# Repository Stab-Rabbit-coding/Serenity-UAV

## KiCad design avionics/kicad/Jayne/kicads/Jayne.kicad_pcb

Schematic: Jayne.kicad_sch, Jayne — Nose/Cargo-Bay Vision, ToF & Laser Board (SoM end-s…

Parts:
CMC5: SRF2012-100Y (CAN); L_CommonModeChoke_Coilcraft_0805USB
C_2V5I, C_2V5O: 1uF; C_0402_1005Metric
C_ISO: 100nF/500V; C_0402_1005Metric
C_VCORE: 1uF; C_0402_1005Metric
C_VISO: 1uF; C_0402_1005Metric
D5: PRTR5V0U2X (CAN); SOT-363_SC-70-6
J_CAM1: CSI CLK/D0; JST_GH_BM04B-GHS-TBT_1x04-1MP_P1.25mm_Vertical
J_CAM2: CAM SDA/SCL/RST/3V3; JST_GH_BM04B-GHS-TBT_1x04-1MP_P1.25mm_Vertical
J_CAM_DS: Direct-solder camera land (nose; DNP if J_CAM* us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; DS_Camera_9P
J_CANFD: 5V/CANH/CANL/GND; JST_GH_BM04B-GHS-TBT_1x04-1MP_P1.25mm_Vertical
J_CHASSIS_R: 0R; R_0402_1005Metric
J_ETH_IN: JST-GH 5P shielded Eth ring; JST_GH_SM05B-GHS-TB_1x05-1MP_P1.25mm_Horizontal
J_ETH_OUT: JST-GH 5P shielded Eth ring; JST_GH_SM05B-GHS-TB_1x05-1MP_P1.25mm_Horizontal
J_LASER: laser +5V/cathode; JST_SH_BM02B-SRSS-TB_1x02-1MP_P1.00mm_Vertical
J_LASER_DS: Direct-solder laser land (nose; DNP if J_LASER us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; DS_Laser_2P
J_PWR: JST-GH 2P +5V/GND; JST_GH_BM02B-GHS-TBT_1x02-1MP_P1.25mm_Vertical
J_SWD: SWD: DIO/CLK/NRST/GND; JST_GH_BM04B-GHS-TBT_1x04-1MP_P1.25mm_Vertical
J_TOF: TFmini-S 5V/GND/TX/RX; JST_GH_BM04B-GHS-TBT_1x04-1MP_P1.25mm_Vertical
J_TOF_DS: Direct-solder ToF land (nose; DNP if J_TOF used); DS_ToF_4P
Q1: AO3400 logic-level N-MOSFET; SOT-23
R1: 100R gate; R_0402_1005Metric
R2: 10k pulldown; R_0402_1005Metric
R_FB1B, R_FB3B: R_fbbot; R_0402_1005Metric
R_FB1T, R_FB3T: R_fbtop; R_0402_1005Metric
R_ISET: 6.04k; R_0402_1005Metric
R_NRST: 10k; R_0402_1005Metric
R_PG1, R_PG3: 100k; R_0402_1005Metric
R_PORZ: 10k; R_0402_1005Metric
R_REXT: 191R; R_0402_1005Metric
R_SHIELD: 0R; R_0402_1005Metric
T1, T2: Wurth 749010012A; Wurth_749010012A_10-100BASE-TX
T1_CMC1, T1_CMC2, T2_CMC1, T2_CMC2: SRF2012-100Y; L_CommonModeChoke_Coilcraft_0805USB
T1_D1, T1_D2, T2_D1, T2_D2: PRTR5V0U2X; SOT-363_SC-70-6
U2: Microchip KSZ9477; TQFP-128-1EP_KSZ9477_14x14mm_P0.4mm_EP10x10
U3: TI MSPM0G3507; QFN-48-1EP_7x7mm_P0.5mm_EP5.15x5.15mm
U4: TI ISOW1044BDFMR; SOIC-20W_7.5x12.8mm_P1.27mm
U5: Infineon SLB9670; QFN-32-1EP_5x5mm_P0.5mm_EP3.45x3.45mm
U_REG_1V2: TLV62569 -> +1V2; SOT-23-6
U_REG_1V2_CI, U_REG_3V3_CI: 10uF; C_0402_1005Metric
U_REG_1V2_CO, U_REG_3V3_CO: 22uF; C_0402_1005Metric
U_REG_1V2_L, U_REG_3V3_L: 2.2uH; L_Taiyo-Yuden_NR-20xx
U_REG_2V5: TLV75725 -> +2V5; SOT-23-5
U_REG_3V3: TLV62569 -> +3V3; SOT-23-6
U_SOM: phyCORE-AM62x PCM-071; phyCORE-AM62x_PCM071_2xBTH-060
Y1: 25MHz; Crystal_SMD_2012-2Pin_2.0x1.2mm

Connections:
+1V2: R_FB1T.1, R_PG1.1, U2.3 (AVDDL), U2.11 (DVDDL), U2.14 (AVDDL), U2.19 (AVDDL), U2.23 (DVDDL), U2.30 (AVDDL), U2.36 (AVDDL), U2.41 (AVDDL), U2.45 (DVDDL), U2.56 (DVDDL), U2.66 (DVDDL), U2.70 (DVDDL), U2.71 (VDDLS), U2.84 (VDDLS), U2.87 (DVDDL), U2.104 (DVDDL), U2.110 (DVDDL), U2.114 (AVDDL), U2.119 (AVDDL), U2.124 (AVDDL), U_REG_1V2_CO.1, U_REG_1V2_L.2
+1V2_PG: R_PG1.2, U_REG_1V2.6 (PG)
+2V5: C_2V5O.1, U2.10 (AVDDH), U2.22 (AVDDH), U2.33 (AVDDH), U2.44 (AVDDH), U2.72 (VDDHS), U2.83 (VDDHS), U2.111 (AVDDH), U2.122 (AVDDH), U2.128 (AVDDH), U_REG_2V5.5 (OUT)
+3V3: C_2V5I.1, J_CAM2.4, J_CAM_DS.8, R_FB3T.1, R_NRST.1, R_PG3.1, R_PORZ.1, U2.61 (VDDIO), U2.68 (VDDIO), U2.99 (VDDIO), U3.6 (VDD), U4.1 (VIO), U5.7 (PP), U5.8 (VDD), U5.22 (VDD), U_REG_2V5.1 (IN), U_REG_2V5.3 (EN), U_REG_3V3_CO.1, U_REG_3V3_L.2, U_SOM.B1 (SoC_VDDSHV5_SDIO), U_SOM.B2 (VBAT); also elsewhere on the board
+3V3_PG: R_PG3.2, U_REG_3V3.6 (PG)
+5V: J_CANFD.1, J_LASER.1, J_LASER_DS.1, J_PWR.2, J_TOF.1, J_TOF_DS.1, U4.9 (VDD), U_REG_1V2.1 (EN), U_REG_1V2.4 (VIN), U_REG_1V2_CI.1, U_REG_3V3.1 (EN), U_REG_3V3.4 (VIN), U_REG_3V3_CI.1, U_SOM.A1 (VIN), U_SOM.A2 (VIN), U_SOM.A3 (VIN)
CAM_RESET_N: J_CAM2.3, J_CAM_DS.7, U_SOM.A56 (X_WKUP_UART0_CTSN)
CAM_SCL: J_CAM2.2, J_CAM_DS.6, U_SOM.C32 (X_I2C1_SCL)
CAM_SDA: J_CAM2.1, J_CAM_DS.5, U_SOM.C33 (X_I2C1_SDA)
CANFD_H: CMC5.2 (L1B), D5.1 (A1), J_CANFD.2
CANFD_ISOGND: C_VISO.2, U4.11 (GND2), U4.15 (GISOIN), U4.16 (GISOIN), U4.17 (GISOIN)
CANFD_ISO_H: CMC5.1 (L1A), U4.19 (CANH)
CANFD_ISO_L: CMC5.3 (L2A), U4.18 (CANL)
CANFD_L: CMC5.4 (L2B), D5.2 (A2), J_CANFD.3
CANFD_RX: U3.28 (PA13), U4.5 (RXD)
CANFD_TX: U3.27 (PA12), U4.3 (TXD)
CANFD_VISO: C_VISO.1, U4.12 (VISOOUT), U4.13 (VSIN), U4.20 (VISOIN)
CSI_CLK_N: J_CAM1.2, J_CAM_DS.2, U_SOM.B32 (X_CSI0_RXCLKN)
CSI_CLK_P: J_CAM1.1, J_CAM_DS.1, U_SOM.B31 (X_CSI0_RXCLKP)
CSI_D0_N: J_CAM1.4, J_CAM_DS.4, U_SOM.A36 (X_CSI0_RXN0)
CSI_D0_P: J_CAM1.3, J_CAM_DS.3, U_SOM.A35 (X_CSI0_RXP0)
ETH_IN_KSZ_RXN: T1.4 (PHY_RXN), U2.5 (TXRX1M_B)
ETH_IN_KSZ_RXP: T1.3 (PHY_RXP), U2.4 (TXRX1P_B)
ETH_IN_KSZ_TXN: T1.2 (PHY_TXN), U2.2 (TXRX1M_A)
ETH_IN_KSZ_TXP: T1.1 (PHY_TXP), U2.1 (TXRX1P_A)
ETH_IN_LRXN: T1.8 (LINE_RXN), T1_CMC2.3 (L2A)
ETH_IN_LRXP: T1.7 (LINE_RXP), T1_CMC2.1 (L1A)
ETH_IN_LTXN: T1.6 (LINE_TXN), T1_CMC1.3 (L2A)
ETH_IN_LTXP: T1.5 (LINE_TXP), T1_CMC1.1 (L1A)
ETH_IN_RXN: J_ETH_IN.5, T1_CMC2.4 (L2B), T1_D2.2 (A2)
ETH_IN_RXP: J_ETH_IN.4, T1_CMC2.2 (L1B), T1_D2.1 (A1)
ETH_IN_TXN: J_ETH_IN.3, T1_CMC1.4 (L2B), T1_D1.2 (A2)
ETH_IN_TXP: J_ETH_IN.2, T1_CMC1.2 (L1B), T1_D1.1 (A1)
ETH_OUT_KSZ_RXN: T2.4 (PHY_RXN), U2.16 (TXRX2M_B)
ETH_OUT_KSZ_RXP: T2.3 (PHY_RXP), U2.15 (TXRX2P_B)
ETH_OUT_KSZ_TXN: T2.2 (PHY_TXN), U2.13 (TXRX2M_A)
ETH_OUT_KSZ_TXP: T2.1 (PHY_TXP), U2.12 (TXRX2P_A)
ETH_OUT_LRXN: T2.8 (LINE_RXN), T2_CMC2.3 (L2A)
ETH_OUT_LRXP: T2.7 (LINE_RXP), T2_CMC2.1 (L1A)
ETH_OUT_LTXN: T2.6 (LINE_TXN), T2_CMC1.3 (L2A)
ETH_OUT_LTXP: T2.5 (LINE_TXP), T2_CMC1.1 (L1A)
ETH_OUT_RXN: J_ETH_OUT.5, T2_CMC2.4 (L2B), T2_D2.2 (A2)
ETH_OUT_RXP: J_ETH_OUT.4, T2_CMC2.2 (L1B), T2_D2.1 (A1)
ETH_OUT_TXN: J_ETH_OUT.3, T2_CMC1.4 (L2B), T2_D1.2 (A2)
ETH_OUT_TXP: J_ETH_OUT.2, T2_CMC1.2 (L1B), T2_D1.1 (A1)
GND: C_2V5I.2, C_2V5O.2, C_ISO.1, C_VCORE.2, J_CAM_DS.9, J_CANFD.4, J_CHASSIS_R.1, J_PWR.1, J_SWD.4, J_TOF.2, J_TOF_DS.2, Q1.2 (S), R2.2, R_FB1B.2, R_FB3B.2, R_ISET.2, R_REXT.2, T1_D1.3 (K), T1_D2.3 (K), T2_D1.3 (K), T2_D2.3 (K), U2.46 (GND), U2.47 (GND), U2.69 (GND), U2.75 (GND), U2.77 (GND), U2.80 (GND), U2.107 (GND), U2.109 (GND), U2.123 (GND), U2.129 (GND), U3.7 (VSS), U3.49 (VSS), U4.4 (STB), U4.6 (GNDIO), U4.10 (GND1), U5.2 (GND), U5.9 (GND), U5.23 (GND), U5.32 (GND), U_REG_1V2.2 (GND), U_REG_1V2_CI.2, U_REG_1V2_CO.2, U_REG_2V5.2 (GND), U_REG_3V3.2 (GND), U_REG_3V3_CI.2, U_REG_3V3_CO.2, U_SOM.A4 (GND), U_SOM.A9 (GND), U_SOM.A14 (GND), U_SOM.A19 (GND), U_SOM.A24 (GND), U_SOM.A29 (GND), U_SOM.A32 (GND), U_SOM.A37 (GND), U_SOM.A42 (GND), U_SOM.A45 (GND), U_SOM.A50 (GND), U_SOM.A55 (GND), U_SOM.B3 (GND), U_SOM.B8 (GND), U_SOM.B13 (GND), U_SOM.B18 (GND), U_SOM.B23 (GND), U_SOM.B28 (GND), U_SOM.B33 (GND), U_SOM.B38 (GND), U_SOM.B43 (GND), U_SOM.B48 (GND), U_SOM.B53 (GND), U_SOM.B56 (GND), U_SOM.B60 (GND), U_SOM.C6 (GND), U_SOM.C12 (GND), U_SOM.C19 (GND), U_SOM.C24 (GND), U_SOM.C31 (GND), U_SOM.C38 (GND), U_SOM.C43 (GND), U_SOM.C48 (GND), U_SOM.C53 (GND), U_SOM.C59 (GND), U_SOM.D3 (GND), U_SOM.D9 (GND), U_SOM.D17 (GND), U_SOM.D22 (GND)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; also elsewhere on the board
KSZ_ISET: R_ISET.1, U2.127 (ISET)
KSZ_SREXT: R_REXT.1, U2.76 (S_REXT)
KSZ_XI: U2.126 (XI), Y1.1
KSZ_XO: U2.125 (XO), Y1.2
LASER_CATHODE: J_LASER.2, J_LASER_DS.2, Q1.3 (D)
LASER_EN: R1.1, U3.40 (PA22)
LASER_GATE: Q1.1 (G), R1.2, R2.1
MCU_NRST: J_SWD.3, R_NRST.2, U3.4 (NRST)
MCU_SWCLK: J_SWD.2, U3.35 (PA20/SWCLK)
MCU_SWDIO: J_SWD.1, U3.34 (PA19/SWDIO)
MCU_VCORE: C_VCORE.1, U3.48 (VCORE)
PGND: C_ISO.2, D5.3 (K), J_CHASSIS_R.2, R_SHIELD.1
PGND_SHIELD: J_ETH_IN.1, J_ETH_OUT.1, R_SHIELD.2
RGMII_K2S_C: U2.48 (TX_CLK6/REFCLKI6), U_SOM.A18 (X_CPSW_RGMII2_RXC)
RGMII_K2S_CTL: U2.49 (TX_EN6/TX_CTL6), U_SOM.A17 (X_CPSW_RGMII2_RX_CTL)
RGMII_K2S_D0: U2.55 (TXD6_0), U_SOM.A23 (X_CPSW_RGMII2_RD0)
RGMII_K2S_D1: U2.54 (TXD6_1), U_SOM.A22 (X_CPSW_RGMII2_RD1)
RGMII_K2S_D2: U2.53 (TXD6_2), U_SOM.A21 (X_CPSW_RGMII2_RD2)
RGMII_K2S_D3: U2.52 (TXD6_3), U_SOM.A20 (X_CPSW_RGMII2_RD3)
RGMII_S2K_C: U2.57 (RX_CLK6/REFCLKO6), U_SOM.A25 (X_CPSW_RGMII2_TXC)
RGMII_S2K_CTL: U2.58 (RX_DV6/CRS_DV6/RX_CTL6), U_SOM.A26 (X_CPSW_RGMII2_TX_CTL)
RGMII_S2K_D0: U2.65 (RXD6_0), U_SOM.A27 (X_CPSW_RGMII2_TD0)
RGMII_S2K_D1: U2.64 (RXD6_1), U_SOM.A28 (X_CPSW_RGMII2_TD1)
RGMII_S2K_D2: U2.63 (RXD6_2), U_SOM.A30 (X_CPSW_RGMII2_TD2)
RGMII_S2K_D3: U2.62 (RXD6_3), U_SOM.A31 (X_CPSW_RGMII2_TD3)
RS485_DE: U3.14 (PB2); also elsewhere on the board
RS485_RX: U3.26 (PB16); also elsewhere on the board
RS485_TX: U3.25 (PB15); also elsewhere on the board
SOC_PORZ: R_PORZ.2, U_SOM.C52 (X_nRESET_IN)
SW_INT_N: U2.94 (INTRP_N), U3.45 (PA25)
SW_RESET_N: U2.96 (RESET_N), U3.39 (PA21)
SW_SPI_CS: U2.100 (SCS_N), U3.30 (PA15)
SW_SPI_MISO: U2.97 (SDO), U3.31 (PA16)
SW_SPI_MOSI: U2.98 (SDI/SDA/MDIO), U3.33 (PA18)
SW_SPI_SCK: U2.101 (SCL/MDC), U3.32 (PA17)
TPM_PIRQ: U3.46 (PA26), U5.18 (PIRQ#)
TPM_RESET_N: U3.47 (PA27), U5.17 (RST#)
TPM_SPI_CS: U3.8 (PA2), U5.20 (CS#)
TPM_SPI_MISO: U3.10 (PA4), U5.24 (MISO)
TPM_SPI_MOSI: U3.11 (PA5), U5.21 (MOSI)
TPM_SPI_SCK: U3.12 (PA6), U5.19 (SCLK)
UART_A2M: U3.19 (PA11), U_SOM.D38 (X_UART0_TXD)
UART_M2A: U3.18 (PA10), U_SOM.D37 (X_UART0_RXD)
UART_TOF_RX: J_TOF.4, J_TOF_DS.4, U3.17 (PA9)
UART_TOF_TX: J_TOF.3, J_TOF_DS.3, U3.16 (PA8)
U_REG_1V2_FB: R_FB1B.1, R_FB1T.2, U_REG_1V2.5 (FB)
U_REG_1V2_SW: U_REG_1V2.3 (SW), U_REG_1V2_L.1
U_REG_3V3_FB: R_FB3B.1, R_FB3T.2, U_REG_3V3.5 (FB)
U_REG_3V3_SW: U_REG_3V3.3 (SW), U_REG_3V3_L.1

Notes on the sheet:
JAYNE — Nose/Cargo Vision/ToF/Laser | STANDALONE board (NOT a PB2-I cape) | SoM end-state: PHYTEC PCM-071 + carrier (KSZ9477 / MSPM0G3507 / SLB9670 / ISOW1044)
=== Section A: Power Input + Carrier Rails ===
Carrier rails (design decision 2026-07-13): PCM-071 provides NO rail to the carrier; all generated here from +5V. Feedback dividers / inductor / LDO margin are first-pass — verify per TI datasheet design procedures.
=== Section B: PHYTEC phyCORE PCM-071 SoM (U_SOM) ===
=== Section C: Microchip KSZ9477 (U2) ===
=== Section D: MSPM0G3507 (U3) + SLB9670 TPM (U5) ===
=== Section E: ISOW1044 Isolated CAN-FD (U4) ===
=== Section F: Ethernet Ring EMI Chain (in / out) ===
=== Section G: PGND/GND single-point bond ===
=== Section H: Camera / ToF / Laser ===

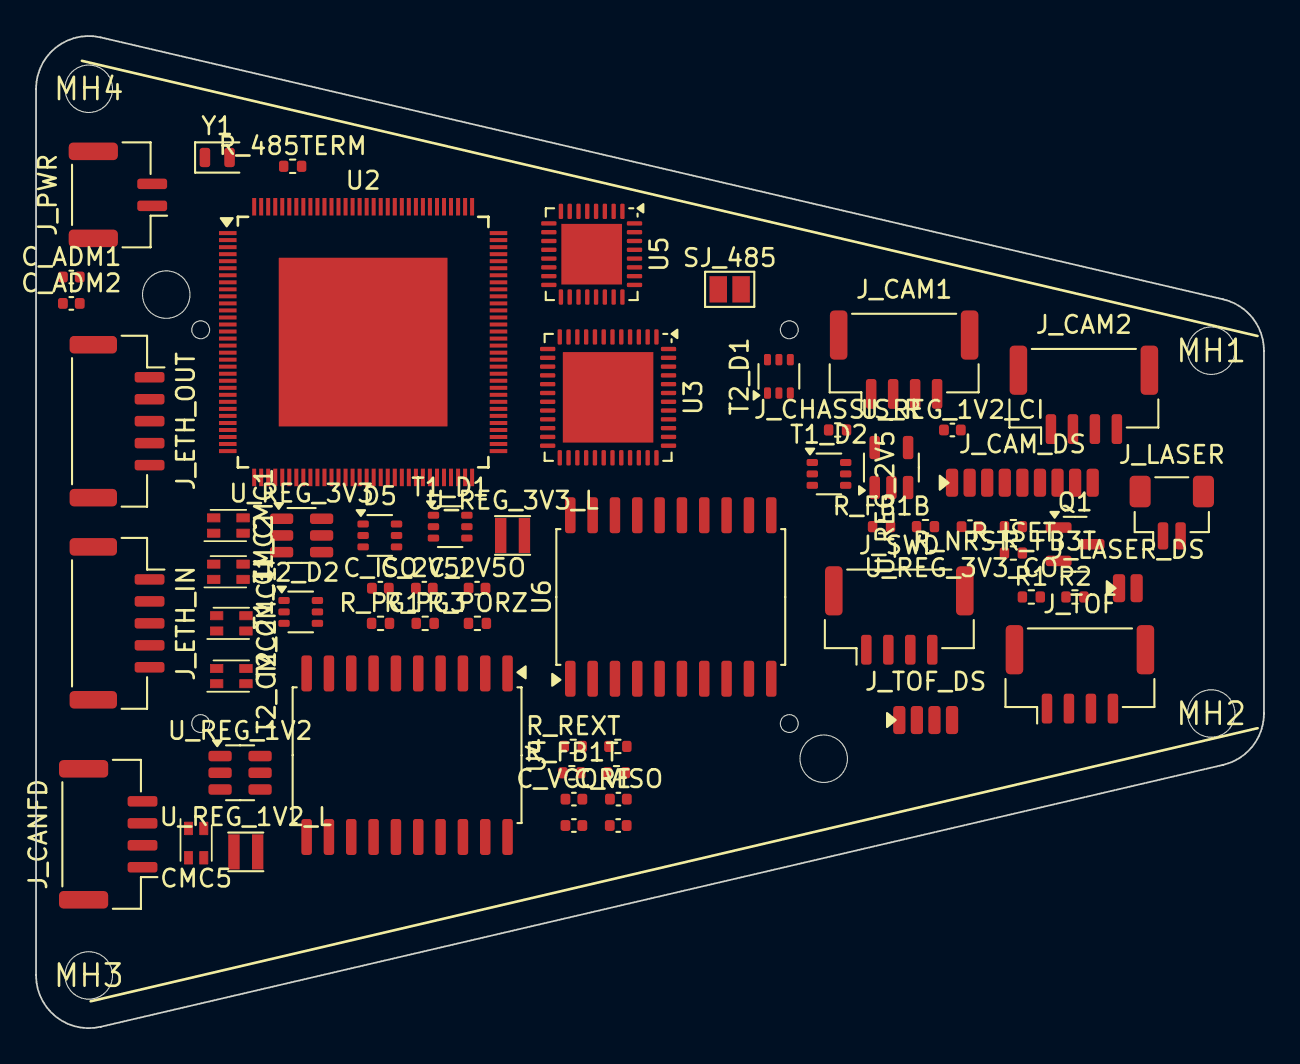
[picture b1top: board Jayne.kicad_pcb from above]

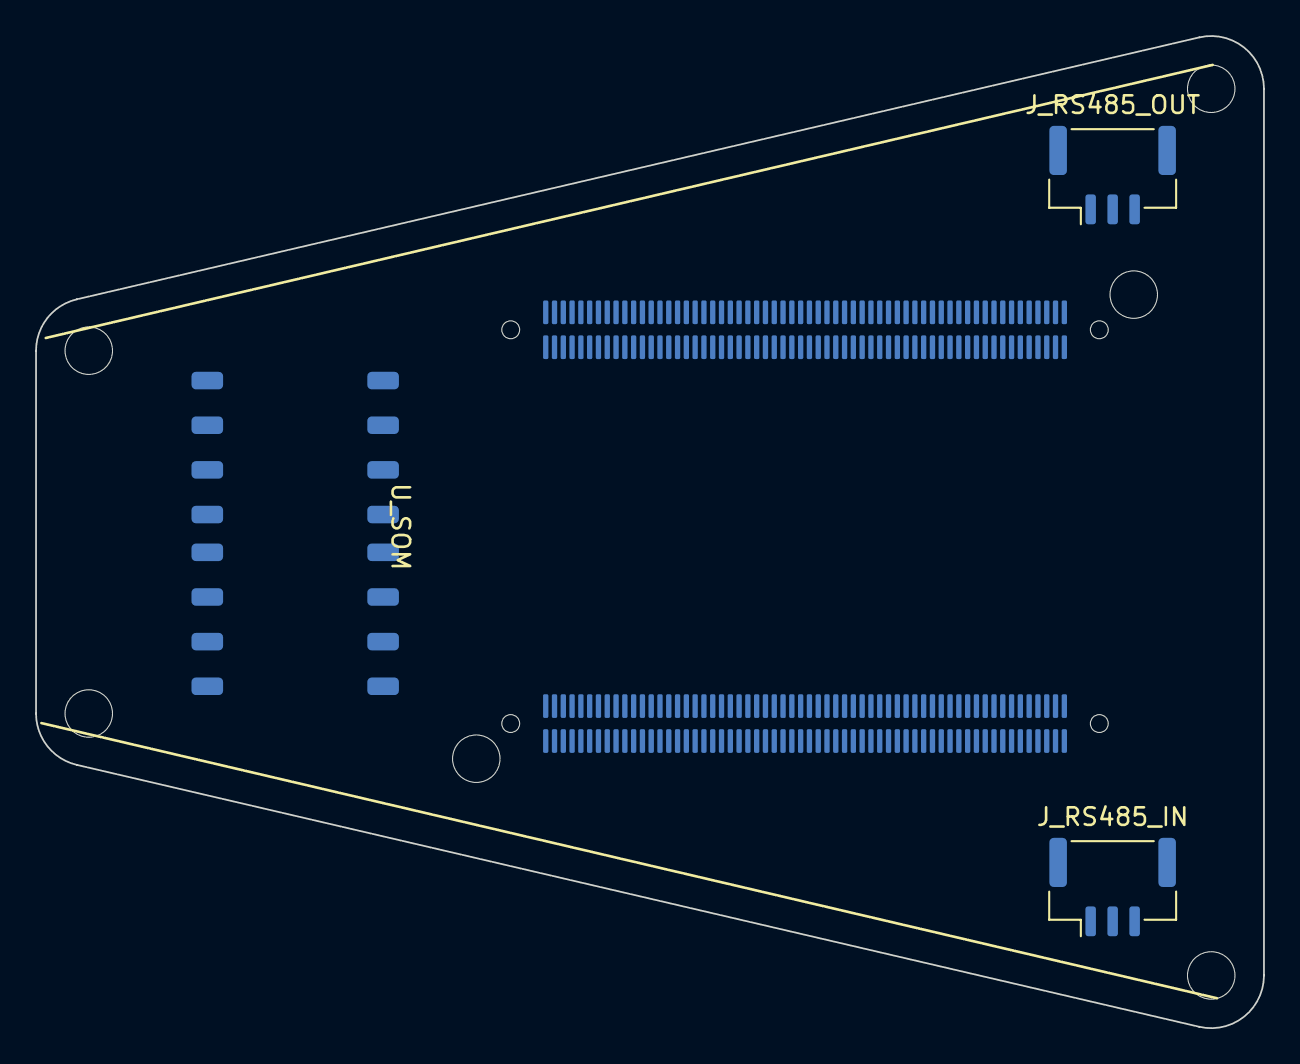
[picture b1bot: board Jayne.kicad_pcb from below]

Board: 4 copper layers, 69.8 x 56.4 mm, 70 parts (5 on the bottom side), 100 nets, no tracks yet.

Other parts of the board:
C_ADM1, C_ADM2: 100nF; C_0402_1005Metric
J_RS485_IN: RS-485 trunk IN (A/B/GND); JST_GH_BM03B-GHS-TBT_1x03-1MP_P1.25mm_Vertical
J_RS485_OUT: RS-485 trunk OUT (A/B/GND); JST_GH_BM03B-GHS-TBT_1x03-1MP_P1.25mm_Vertical
MH1, MH2, MH3, MH4: (no value)
R_485TERM: 120R; R_0402_1005Metric
SJ_485: open by default; SolderJumper-2_P1.3mm_Open_Pad1.0x1.5mm
U6: TI ISOW1412; SOIC-20W_7.5x12.8mm_P1.27mm

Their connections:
+3V3: C_ADM1.1, U6.1, U6.9; also elsewhere on the board
GND: C_ADM1.2, U6.6, U6.10; also elsewhere on the board
ISO_3V3_485: C_ADM2.1, U6.12, U6.16
ISO_GND_485: C_ADM2.2, J_RS485_IN.3, J_RS485_OUT.3, U6.11, U6.13, U6.15
RS485_A: J_RS485_IN.1, J_RS485_OUT.1, R_485TERM.1, U6.17, U6.20
RS485_B: J_RS485_IN.2, J_RS485_OUT.2, SJ_485.2, U6.18, U6.19
RS485_DE: U6.3, U6.5; also elsewhere on the board
RS485_RX: U6.4; also elsewhere on the board
RS485_TX: U6.2; also elsewhere on the board
TERM485_MID: R_485TERM.2, SJ_485.1

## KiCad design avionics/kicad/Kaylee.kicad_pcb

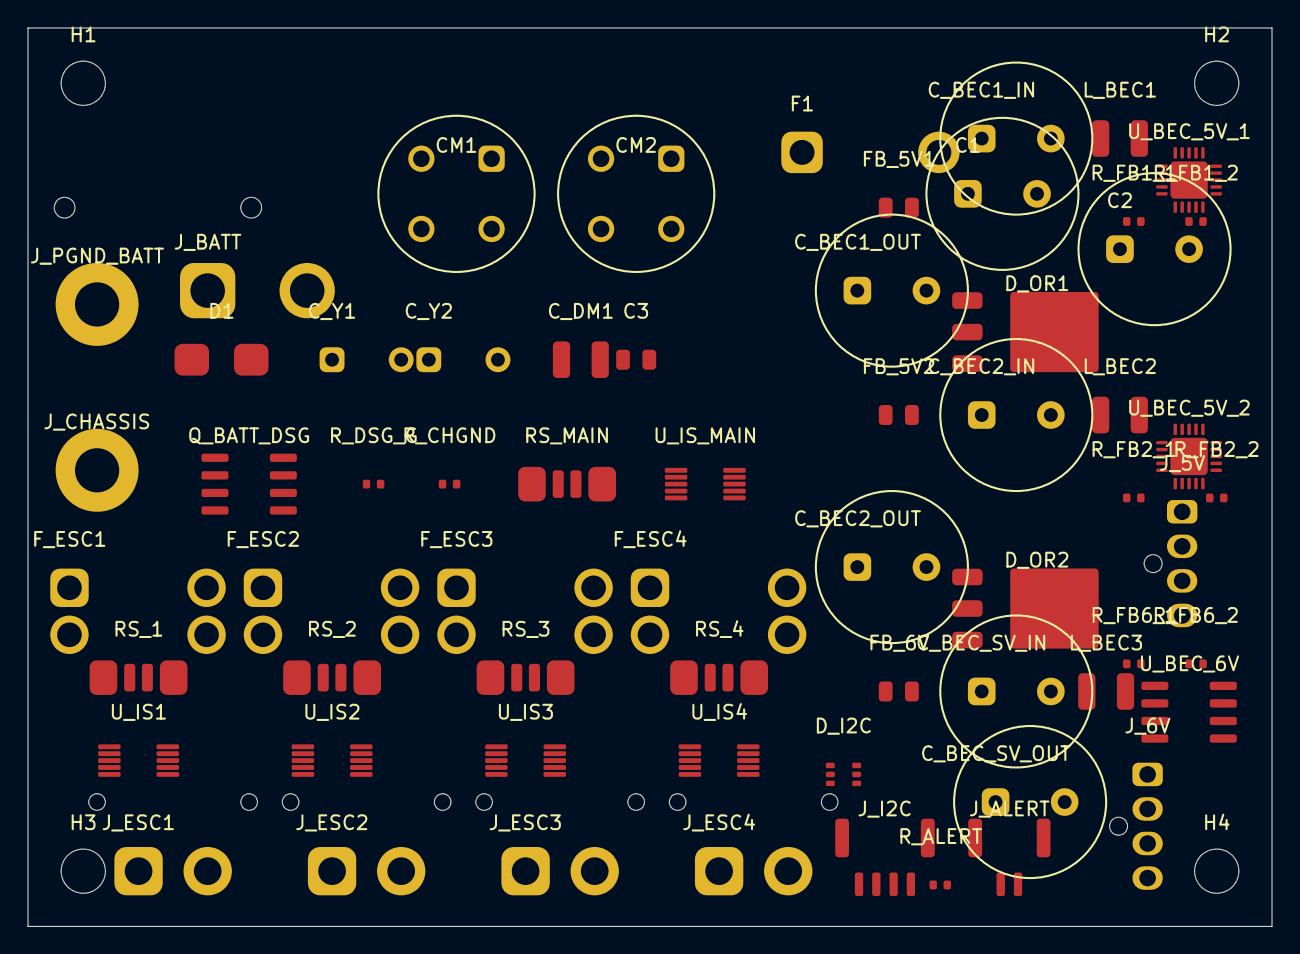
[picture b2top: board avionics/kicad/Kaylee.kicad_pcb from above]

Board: 4 copper layers, 90.0 x 65.0 mm, 67 parts (0 on the bottom side), 36 nets, no tracks yet.

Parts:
C1, C2: 220uF/35V; CP_Radial_D10.0mm_P5.00mm
C3: 100nF/50V; C_0805_2012Metric
CM1, CM2: WE-SL5_7440640500; CMC_WE-SL5_7440640500
C_BEC1_IN, C_BEC1_OUT, C_BEC2_IN, C_BEC2_OUT: 100uF/50V; CP_Radial_D10.0mm_P5.00mm
C_BEC_SV_IN: 100uF/50V; CP_Radial_D10.0mm_P5.00mm
C_BEC_SV_OUT: 100uF/50V; CP_Radial_D10.0mm_P5.00mm
C_DM1: 10uF/50V; L_1210_3225Metric
C_Y1, C_Y2: 4.7nF/250V_Y2; C_Disc_D4.3mm_W1.9mm_P5.00mm
D1: SMBJ33CA; D_SMB
D_I2C: PRTR5V0U2X; SOT-363_SC-70-6
D_OR1, D_OR2: MBRD1045CT; TO-252-3_TabPin2
F1: FuseHolder_MAXI_150A; FuseHolder_MAXI_PCB
FB_5V1, FB_5V2, FB_6V: WE-742792612; C_0805_2012Metric
F_ESC1, F_ESC2, F_ESC3, F_ESC4: FuseHolder_Mini_40A; Fuseholder_Blade_Mini_Keystone_3568
H1, H2, H3, H4: M3; MountingHole_3.2mm_M3
J_5V: NanoFit-4P_5V; Molex_Nano-Fit_105309-xx04_1x04_P2.50mm_Vertical
J_6V: NanoFit-4P_6V; Molex_Nano-Fit_105309-xx04_1x04_P2.50mm_Vertical
J_ALERT: JST-GH_2P_ALERT; JST_GH_BM02B-GHS-TBT_1x02-1MP_P1.25mm_Vertical
J_BATT: XT60PW-F; AMASS_XT60PW-F_1x02_P7.20mm_Horizontal
J_CHASSIS: M3_Lug; MountingHole_3.2mm_M3_Pad_Via
J_ESC1: XT30PW-F_ESC1; AMASS_XT30PW-F_1x02_P2.50mm_Horizontal
J_ESC2: XT30PW-F_ESC2; AMASS_XT30PW-F_1x02_P2.50mm_Horizontal
J_ESC3: XT30PW-F_ESC3; AMASS_XT30PW-F_1x02_P2.50mm_Horizontal
J_ESC4: XT30PW-F_ESC4; AMASS_XT30PW-F_1x02_P2.50mm_Horizontal
J_I2C: JST-GH_4P_I2C; JST_GH_BM04B-GHS-TBT_1x04-1MP_P1.25mm_Vertical
J_PGND_BATT: M3_Lug; MountingHole_3.2mm_M3_Pad_Via
L_BEC1, L_BEC2, L_BEC3: WE-744314100_10uH; L_1210_3225Metric
Q_BATT_DSG: AON6556; SOIC-8_3.9x4.9mm_P1.27mm
RS_1, RS_2, RS_3, RS_4: 1mOhm_Kelvin_2512; R_Shunt_CSS2H_2512K
RS_MAIN: 1mOhm_Kelvin_2512; R_Shunt_CSS2H_2512K
R_ALERT: 2.2k; R_0402_1005Metric
R_CHGND: 0R; R_0402_1005Metric
R_DSG_G: 10k; R_0402_1005Metric
R_FB1_1, R_FB2_1, R_FB6_1: 100k; R_0402_1005Metric
R_FB1_2, R_FB2_2: 22.1k; R_0402_1005Metric
R_FB6_2: 30.1k; R_0402_1005Metric
U_BEC_5V_1, U_BEC_5V_2: TPS54620RGYT; Texas_RGP0020D_VQFN-20-1EP_4x4mm_P0.5mm_EP2.7x2.7mm
U_BEC_6V: TPS54540DDAR; SOIC-8_3.9x4.9mm_P1.27mm
U_IS1: INA226_0x40; MSOP-10_3x3mm_P0.5mm
U_IS2: INA226_0x41; MSOP-10_3x3mm_P0.5mm
U_IS3: INA226_0x42; MSOP-10_3x3mm_P0.5mm
U_IS4: INA226_0x43; MSOP-10_3x3mm_P0.5mm
U_IS_MAIN: INA226_0x44; MSOP-10_3x3mm_P0.5mm

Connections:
+5V: D_I2C.6, D_OR1.2, D_OR2.2, J_5V.3, J_5V.4, J_I2C.2, R_ALERT.1, U_IS1.4, U_IS2.4, U_IS3.4, U_IS4.4, U_IS_MAIN.4
+6V: C_BEC_SV_OUT.1, J_6V.3, J_6V.4, R_FB6_1.1, U_BEC_6V.6
BEC1_PRE_OR: C_BEC1_OUT.1, D_OR1.1, R_FB1_1.1, U_BEC_5V_1.11
BEC1_SW: L_BEC1.2, U_BEC_5V_1.5, U_BEC_5V_1.6
BEC1_VIN_F: C_BEC1_IN.1, FB_5V1.2, L_BEC1.1, U_BEC_5V_1.1, U_BEC_5V_1.15, U_BEC_5V_1.16, U_BEC_5V_1.17, U_BEC_5V_1.18, U_BEC_5V_1.19, U_BEC_5V_1.20
BEC2_PRE_OR: C_BEC2_OUT.1, D_OR1.3, D_OR2.1, D_OR2.3, R_FB2_1.1, U_BEC_5V_2.11
BEC2_SW: L_BEC2.2, U_BEC_5V_2.5, U_BEC_5V_2.6
BEC2_VIN_F: C_BEC2_IN.1, FB_5V2.2, L_BEC2.1, U_BEC_5V_2.1, U_BEC_5V_2.15, U_BEC_5V_2.16, U_BEC_5V_2.17, U_BEC_5V_2.18, U_BEC_5V_2.19, U_BEC_5V_2.20
BEC6V_SW: L_BEC3.2, U_BEC_6V.8
BEC6V_VIN_F: C_BEC_SV_IN.1, FB_6V.2, L_BEC3.1, U_BEC_6V.2, U_BEC_6V.3, U_BEC_6V.4
CHASSIS: C_Y1.2, C_Y2.2, R_CHGND.2
DSG_GATE: Q_BATT_DSG.8, R_DSG_G.1
ESC1_FUSED: F_ESC1.2, RS_1.1, U_IS1.10
ESC1_RS_OUT: J_ESC1.1, RS_1.4
ESC1_SNS_N: RS_1.3, U_IS1.2
ESC1_SNS_P: RS_1.2, U_IS1.1
ESC2_FUSED: F_ESC2.2, RS_2.1, U_IS2.10
ESC2_RS_OUT: J_ESC2.1, RS_2.4
ESC2_SNS_N: RS_2.3, U_IS2.2
ESC2_SNS_P: RS_2.2, U_IS2.1
ESC3_FUSED: F_ESC3.2, RS_3.1, U_IS3.10
ESC3_RS_OUT: J_ESC3.1, RS_3.4
ESC3_SNS_N: RS_3.3, U_IS3.2
ESC3_SNS_P: RS_3.2, U_IS3.1
ESC4_FUSED: F_ESC4.2, RS_4.1, U_IS4.10
ESC4_RS_OUT: J_ESC4.1, RS_4.4
ESC4_SNS_N: RS_4.3, U_IS4.2
ESC4_SNS_P: RS_4.2, U_IS4.1
MAIN_SNS_N: RS_MAIN.3, U_IS_MAIN.2
MAIN_SNS_P: RS_MAIN.2, U_IS_MAIN.1
PDB_ALERT_N: J_ALERT.2, R_ALERT.2, U_IS1.7, U_IS2.7, U_IS3.7, U_IS4.7, U_IS_MAIN.7
PDB_SCL: D_I2C.4, J_I2C.3, U_IS1.6, U_IS2.6, U_IS3.6, U_IS4.6, U_IS_MAIN.6
PDB_SDA: D_I2C.5, J_I2C.4, U_IS1.5, U_IS2.5, U_IS3.5, U_IS4.5, U_IS_MAIN.5
PGND: C1.2, C2.2, C3.2, CM1.3, CM1.4, CM2.3, CM2.4, C_BEC1_IN.2, C_BEC1_OUT.2, C_BEC2_IN.2, C_BEC2_OUT.2, C_BEC_SV_IN.2, C_BEC_SV_OUT.2, C_DM1.2, C_Y2.1, D1.1, D_I2C.1, J_5V.1, J_5V.2, J_6V.1, J_6V.2, J_ALERT.1, J_BATT.2, J_ESC1.2, J_ESC2.2, J_ESC3.2, J_ESC4.2, J_I2C.1, R_CHGND.1, R_DSG_G.2, R_FB1_2.2, R_FB2_2.2, R_FB6_2.2, U_BEC_5V_1.7, U_BEC_5V_1.8, U_BEC_5V_1.9, U_BEC_5V_1.10, U_BEC_5V_1.21, U_BEC_5V_2.7, U_BEC_5V_2.8, U_BEC_5V_2.9, U_BEC_5V_2.10, U_BEC_5V_2.21, U_IS1.3, U_IS2.3, U_IS3.3, U_IS4.3, U_IS_MAIN.3
VBAT: F_ESC1.1, F_ESC2.1, F_ESC3.1, F_ESC4.1, Q_BATT_DSG.1, Q_BATT_DSG.2, Q_BATT_DSG.3, Q_BATT_DSG.4, RS_MAIN.1, RS_MAIN.4, U_IS_MAIN.10
VDIS: C1.1, C2.1, C3.1, CM1.1, CM1.2, CM2.1, CM2.2, C_DM1.1, C_Y1.1, D1.2, F1.1, F1.2, FB_5V1.1, FB_5V2.1, FB_6V.1, J_BATT.1, Q_BATT_DSG.5, Q_BATT_DSG.6, Q_BATT_DSG.7

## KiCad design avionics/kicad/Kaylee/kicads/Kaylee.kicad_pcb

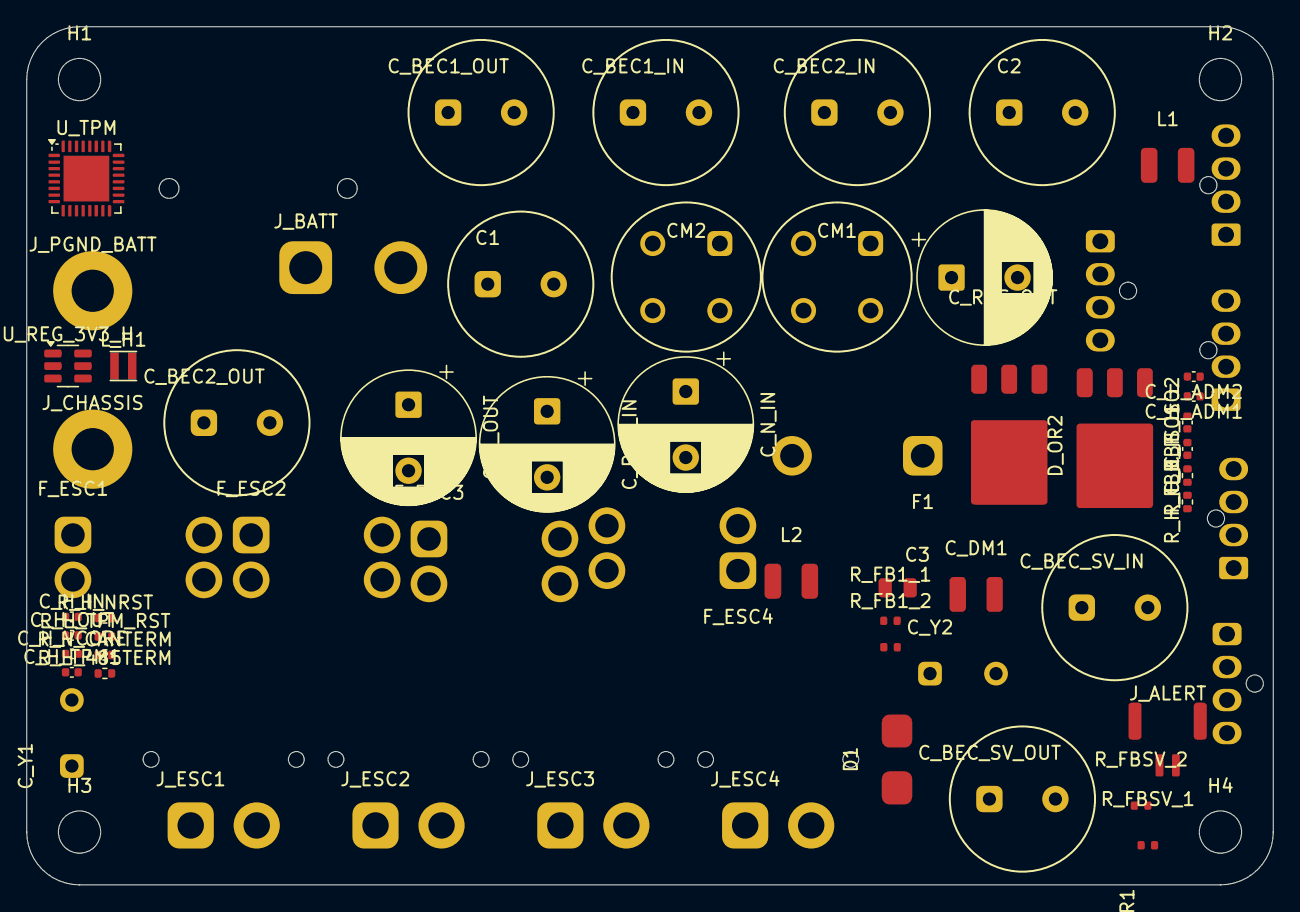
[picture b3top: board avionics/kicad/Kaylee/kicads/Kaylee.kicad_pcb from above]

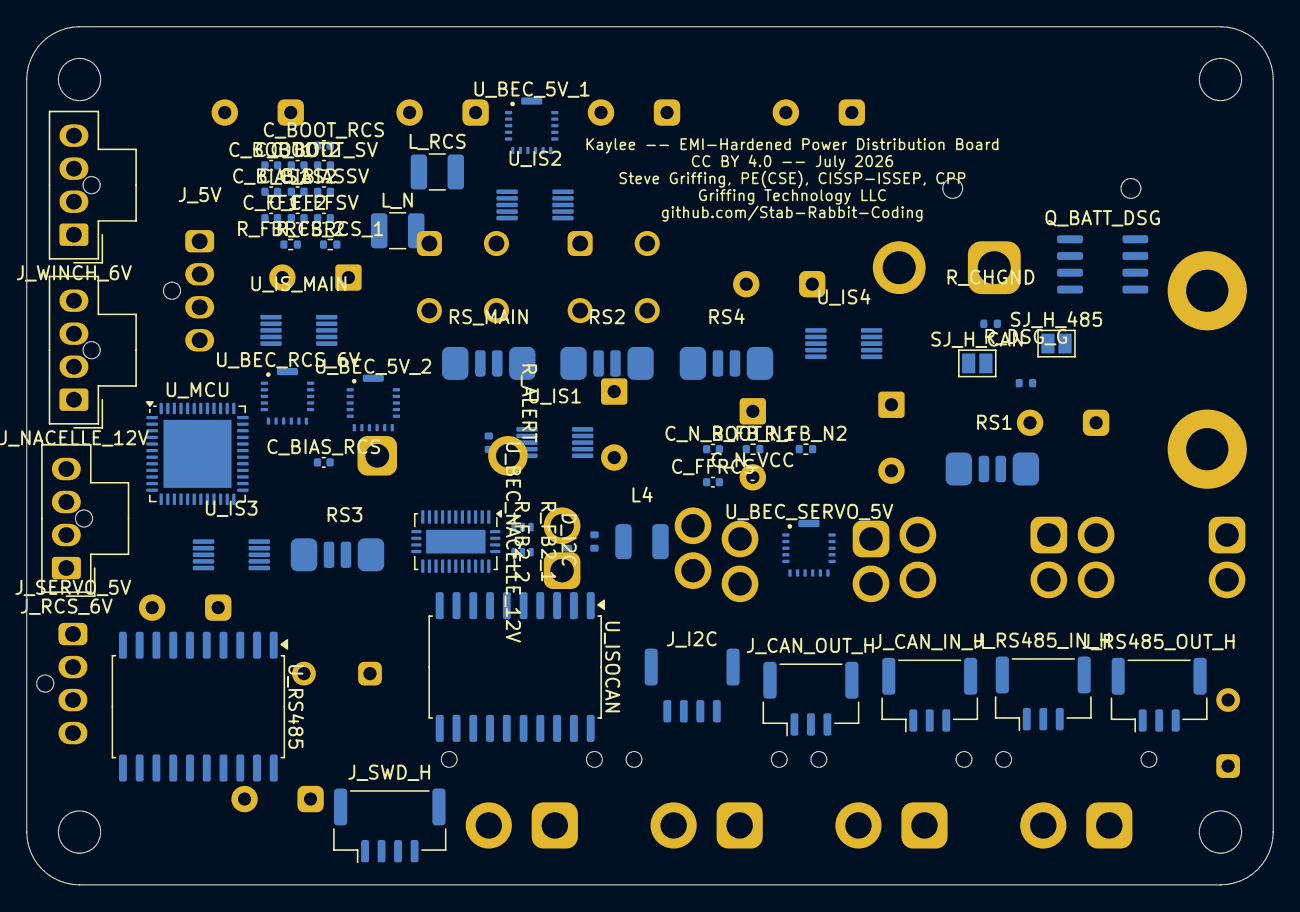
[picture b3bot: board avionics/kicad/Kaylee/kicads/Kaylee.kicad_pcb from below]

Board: 4 copper layers, 94.4 x 65.0 mm, 120 parts (59 on the bottom side), 83 nets, no tracks yet.

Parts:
C1, C2: 220uF/35V; CP_Radial_D10.0mm_P5.00mm
C3: 100nF/50V; C_0805_2012Metric
CM1, CM2: WE-SL5_7440640500; CMC_WE-SL5_7440640500
C_BEC1_IN, C_BEC1_OUT, C_BEC2_IN, C_BEC2_OUT: 100uF/50V; CP_Radial_D10.0mm_P5.00mm
C_BEC_SV_IN: 100uF/50V; CP_Radial_D10.0mm_P5.00mm
C_BEC_SV_OUT: 100uF/50V; CP_Radial_D10.0mm_P5.00mm
C_BIAS1, C_BIAS2: 2.2uF ceramic (BIAS to GND); C_0402_1005Metric
C_BIASSV: 2.2uF ceramic (BIAS to GND); C_0402_1005Metric
C_BIAS_RCS: 2.2uF ceramic (BIAS to GND); C_0402_1005Metric
C_BOOT1, C_BOOT2: 0.1uF X7R (BST-LX); C_0402_1005Metric
C_BOOT_RCS: 0.1uF X7R (BST-LX); C_0402_1005Metric
C_BOOT_SV: 0.1uF X7R (BST-LX); C_0402_1005Metric
C_DM1: 10uF/50V; L_1210_3225Metric
C_FF1, C_FF2: 50pF NP0 (feedforward); C_0402_1005Metric
C_FFRCS: 82pF NP0 (feedforward); C_0402_1005Metric
C_FFSV: 78pF NP0 (feedforward); C_0402_1005Metric
C_H_ADM1, C_H_ADM2: 100nF; C_0402_1005Metric
C_H_IN: 10uF; C_0402_1005Metric
C_H_ISO1: 100nF; C_0402_1005Metric
C_H_ISO2: 1uF; C_0402_1005Metric
C_H_OUT: 22uF; C_0402_1005Metric
C_H_TPM1: 100nF; C_0402_1005Metric
C_H_VCORE: 1uF; C_0402_1005Metric
C_N_BOOT: 0.47uF >=6.3V (BOOT-SW); C_0402_1005Metric
C_N_IN: 0.1uF+4.7uF ceramic (PVIN bypass); CP_Radial_D10.0mm_P5.00mm
C_N_OUT: 90uF eff, >=16V rated; CP_Radial_D10.0mm_P5.00mm
C_N_VCC: 2.2uF ceramic (VCC to GND); C_0402_1005Metric
C_RCS_IN: 0.1uF+4.7uF ceramic (SUP bypass); CP_Radial_D10.0mm_P5.00mm
C_RCS_OUT: 88uF eff; CP_Radial_D10.0mm_P5.00mm
C_Y1, C_Y2: 4.7nF/250V_Y2; C_Disc_D4.3mm_W1.9mm_P5.00mm
D1: SMBJ33CA; D_SMB
D_I2C: PRTR5V0U2X; SOT-363_SC-70-6
D_OR1, D_OR2: MBRD1045CT; TO-252-3_TabPin2
F1: FuseHolder_MAXI_150A; FuseHolder_MAXI_PCB
F_ESC1, F_ESC2, F_ESC3, F_ESC4: FuseHolder_Mini_40A; Fuseholder_Blade_Mini_Keystone_3568
H1, H2, H3, H4: M3; MountingHole_3.2mm_M3
J_5V: NanoFit-4P_5V; Molex_Nano-Fit_105309-xx04_1x04_P2.50mm_Vertical
J_ALERT: JST-GH_2P_ALERT; JST_GH_BM02B-GHS-TBT_1x02-1MP_P1.25mm_Vertical
J_BATT: XT60PW-F; AMASS_XT60PW-F_1x02_P7.20mm_Horizontal
J_CAN_IN_H: CAN-FD trunk IN; JST_GH_BM03B-GHS-TBT_1x03-1MP_P1.25mm_Vertical
J_CAN_OUT_H: CAN-FD trunk OUT; JST_GH_BM03B-GHS-TBT_1x03-1MP_P1.25mm_Vertical
J_CHASSIS: M3_Lug; MountingHole_3.2mm_M3_Pad_Via
J_ESC1: XT30PW-F_ESC1; AMASS_XT30PW-F_1x02_P2.50mm_Horizontal
J_ESC2: XT30PW-F_ESC2; AMASS_XT30PW-F_1x02_P2.50mm_Horizontal
J_ESC3: XT30PW-F_ESC3; AMASS_XT30PW-F_1x02_P2.50mm_Horizontal
J_ESC4: XT30PW-F_ESC4; AMASS_XT30PW-F_1x02_P2.50mm_Horizontal
J_I2C: JST-GH_4P_I2C; JST_GH_BM04B-GHS-TBT_1x04-1MP_P1.25mm_Vertical
J_NACELLE_12V: Molex Nano-Fit 4P 2.5mm NACELLE-12V bus (3x STS32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; Molex_Nano-Fit_105309-xx04_1x04_P2.50mm_Vertical
J_PGND_BATT: M3_Lug; MountingHole_3.2mm_M3_Pad_Via
J_RCS_6V: Molex Nano-Fit 4P 2.5mm RCS-6V bus (4x RCS valve 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; Molex_Nano-Fit_105309-xx04_1x04_P2.50mm_Vertical
J_RS485_IN_H: RS-485 trunk IN; JST_GH_BM03B-GHS-TBT_1x03-1MP_P1.25mm_Vertical
J_RS485_OUT_H: RS-485 trunk OUT; JST_GH_BM03B-GHS-TBT_1x03-1MP_P1.25mm_Vertical
J_SERVO_5V: NanoFit-4P_6V; Molex_Nano-Fit_105309-xx04_1x04_P2.50mm_Vertical
J_SWD_H: SWD: DIO/CLK/NRST/GND; JST_GH_BM04B-GHS-TBT_1x04-1MP_P1.25mm_Vertical
J_WINCH_6V: Molex Nano-Fit 4P 2.5mm WINCH-6V (STS3215-C001); Molex_Nano-Fit_105309-xx04_1x04_P2.50mm_Vertical
L1, L2, L4: WE-744314100_10uH; L_1210_3225Metric
L_H1: 2.2uH; L_Taiyo-Yuden_NR-20xx
L_N: 6.8uH >=5A Isat; L_1210_3225Metric
L_RCS: 2.2uH >=8A Isat; L_1210_3225Metric
Q_BATT_DSG: AON6556; SOIC-8_3.9x4.9mm_P1.27mm
RS1, RS2, RS3, RS4: 1mOhm_Kelvin_2512; R_Shunt_CSS2H_2512K
RS_MAIN: 1mOhm_Kelvin_2512; R_Shunt_CSS2H_2512K
R_ALERT: 2.2k; R_0402_1005Metric
R_CHGND: 0R; R_0402_1005Metric
R_DSG_G: 10k; R_0402_1005Metric
R_FB1_1, R_FB2_1: 100k; R_0402_1005Metric
R_FB1_2, R_FB2_2: 22.1k; R_0402_1005Metric
R_FBRCS_1: 64.9k 1% (top); R_0402_1005Metric
R_FBRCS_2: 10.0k 1% (bottom); R_0402_1005Metric
R_FBSV_1: 100k; R_0402_1005Metric
R_FBSV_2: 30.1k; R_0402_1005Metric
R_FB_N1: 100k 1% (top); R_0402_1005Metric
R_FB_N2: 9.09k 1% (bottom); R_0402_1005Metric
R_H_485TERM: 120R; R_0402_1005Metric
R_H_CANTERM: 120R; R_0402_1005Metric
R_H_FBB: 20k; R_0402_1005Metric
R_H_FBT: 10k; R_0402_1005Metric
R_H_NRST: 10k; R_0402_1005Metric
R_H_TPM_RST: 10k; R_0402_1005Metric
SJ_H_485: open by default; SolderJumper-2_P1.3mm_Open_Pad1.0x1.5mm
SJ_H_CAN: open by default; SolderJumper-2_P1.3mm_Open_Pad1.0x1.5mm
U_BEC_5V_1, U_BEC_5V_2: MAX42408AFOA 36V/8A sync buck (ADI); MAX42408AFOA_FC2QFN17_3.5x3.75mm
U_BEC_NACELLE_12V: LM76005 60V/5A sync buck (TI); Texas_RNP0030B_WQFN-30-1EP_4x6mm_P0.5mm_EP1.8x4.5mm
U_BEC_RCS_6V: MAX42408AFOA 36V/8A sync buck (ADI); MAX42408AFOA_FC2QFN17_3.5x3.75mm
U_BEC_SERVO_5V: MAX42408AFOA 36V/8A sync buck (ADI); MAX42408AFOA_FC2QFN17_3.5x3.75mm
U_IS1: INA226_0x40; MSOP-10_3x3mm_P0.5mm
U_IS2: INA226_0x41; MSOP-10_3x3mm_P0.5mm
U_IS3: INA226_0x42; MSOP-10_3x3mm_P0.5mm
U_IS4: INA226_0x43; MSOP-10_3x3mm_P0.5mm
U_ISOCAN: TI ISOW1044BDFMR; SOIC-20W_7.5x12.8mm_P1.27mm
U_IS_MAIN: INA226_0x44; MSOP-10_3x3mm_P0.5mm
U_MCU: TI MSPM0G3507; QFN-48-1EP_7x7mm_P0.5mm_EP5.15x5.15mm
U_REG_3V3_H: TLV62569DBVR; SOT-23-6
U_RS485: TI ISOW1412; SOIC-20W_7.5x12.8mm_P1.27mm
U_TPM: Infineon SLB9670; QFN-32-1EP_5x5mm_P0.5mm_EP3.45x3.45mm

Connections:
5V_AVIONICS: D_OR1.3, D_OR2.3, J_5V.1, J_5V.2
+3V3: C_H_ADM1.1, C_H_ISO1.1, C_H_OUT.1, C_H_TPM1.1, L_H1.2, R_H_FBT.1, R_H_NRST.1, R_H_TPM_RST.1, U_ISOCAN.1, U_ISOCAN.9, U_MCU.6, U_MCU.41, U_MCU.42, U_MCU.43, U_MCU.44, U_RS485.1, U_RS485.9, U_TPM.1, U_TPM.8, U_TPM.14, U_TPM.22
+5V: C_H_IN.1, D_I2C.4, D_OR1.2, D_OR2.2, J_I2C.2, R_ALERT.1, U_IS1.4, U_IS2.4, U_IS2.9, U_IS3.4, U_IS4.4, U_IS_MAIN.4, U_IS_MAIN.8, U_REG_3V3_H.1, U_REG_3V3_H.4
BEC1_FB: C_FF1.2, R_FB1_1.2, R_FB1_2.1, U_BEC_5V_1.12
BEC2_FB: C_FF2.2, R_FB2_1.2, R_FB2_2.1, U_BEC_5V_2.12
BEC5V1_RAW: C_BEC1_OUT.1, C_FF1.1, D_OR1.1, L1.2, R_FB1_1.1, U_BEC_5V_1.13
BEC5V2_RAW: C_BEC2_OUT.1, C_FF2.1, D_OR2.1, L2.2, R_FB2_1.1, U_BEC_5V_2.13
BECSV_FB: C_FFSV.2, R_FBSV_1.2, R_FBSV_2.1, U_BEC_SERVO_5V.12
CANFD_FLT_N: U_ISOCAN.8, U_MCU.16
CANFD_RX: U_ISOCAN.5, U_MCU.28
CANFD_TX: U_ISOCAN.3, U_MCU.27
CANTERM_MID_H: R_H_CANTERM.2, SJ_H_CAN.1
CAN_H: J_CAN_IN_H.1, J_CAN_OUT_H.1, R_H_CANTERM.1, U_ISOCAN.19
CAN_L: J_CAN_IN_H.2, J_CAN_OUT_H.2, SJ_H_CAN.2, U_ISOCAN.18
CHASSIS: C_Y1.2, C_Y2.2, R_CHGND.1
CM1_OUT_N: CM1.4, CM2.2
CM1_OUT_P: CM1.3, CM2.1
CM2_OUT_N: C1.2, C2.2, C3.2, CM2.4, C_BEC1_IN.2, C_BEC1_OUT.2, C_BEC2_IN.2, C_BEC2_OUT.2, C_BEC_SV_IN.2, C_BEC_SV_OUT.2, C_BIAS1.2, C_BIAS2.2, C_BIASSV.2, C_BIAS_RCS.2, C_DM1.2, C_H_ADM1.2, C_H_IN.2, C_H_ISO1.2, C_H_OUT.2, C_H_TPM1.2, C_H_VCORE.1, C_H_VCORE.2, C_N_IN.2, C_N_OUT.2, C_N_VCC.2, C_RCS_IN.2, C_RCS_OUT.2, C_Y2.1, D1.2, D_I2C.1, J_5V.3, J_5V.4, J_ALERT.1, J_ESC1.2, J_ESC2.2, J_ESC3.2, J_ESC4.2, J_I2C.1, J_NACELLE_12V.1, J_NACELLE_12V.2, J_RCS_6V.1, J_RCS_6V.2, J_SERVO_5V.1, J_SERVO_5V.2, J_SWD_H.4, J_WINCH_6V.1, J_WINCH_6V.2, Q_BATT_DSG.2, R_CHGND.2, R_FB1_2.2, R_FB2_2.2, R_FBRCS_2.2, R_FBSV_2.2, R_FB_N2.2, R_H_FBB.2, U_BEC_5V_1.4, U_BEC_5V_1.5, U_BEC_5V_1.7, U_BEC_5V_1.8, U_BEC_5V_1.10, U_BEC_5V_1.16, U_BEC_5V_2.4, U_BEC_5V_2.5, U_BEC_5V_2.7, U_BEC_5V_2.8, U_BEC_5V_2.10, U_BEC_5V_2.16, U_BEC_NACELLE_12V.13, U_BEC_NACELLE_12V.14, U_BEC_NACELLE_12V.15, U_BEC_NACELLE_12V.17, U_BEC_NACELLE_12V.24, U_BEC_NACELLE_12V.25, U_BEC_NACELLE_12V.26, U_BEC_RCS_6V.4, U_BEC_RCS_6V.5, U_BEC_RCS_6V.7, U_BEC_RCS_6V.8, U_BEC_RCS_6V.10, U_BEC_RCS_6V.16, U_BEC_SERVO_5V.4, U_BEC_SERVO_5V.5, U_BEC_SERVO_5V.7, U_BEC_SERVO_5V.8, U_BEC_SERVO_5V.10, U_BEC_SERVO_5V.16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
CM2_OUT_P: CM2.3, F1.1
DSG_GATE: Q_BATT_DSG.1, Q_BATT_DSG.8, R_DSG_G.2
ESC1_RS_OUT: J_ESC1.1, RS1.4, U_IS1.10
ESC1_RS_SN: RS1.3, U_IS1.2
ESC1_RS_SP: RS1.2, U_IS1.1
ESC2_RS_OUT: J_ESC2.1, RS2.4, U_IS2.10
ESC2_RS_SN: RS2.3, U_IS2.2
ESC2_RS_SP: RS2.2, U_IS2.1
ESC3_RS_OUT: J_ESC3.1, RS3.4, U_IS3.10
ESC3_RS_SN: RS3.3, U_IS3.2
ESC3_RS_SP: RS3.2, U_IS3.1
ESC4_RS_OUT: J_ESC4.1, RS4.4, U_IS4.10
ESC4_RS_SN: RS4.3, U_IS4.2
ESC4_RS_SP: RS4.2, U_IS4.1
ISO_3V3_485: C_H_ADM2.1, U_RS485.12, U_RS485.16
ISO_5V_CAN: C_H_ISO2.1, U_ISOCAN.12, U_ISOCAN.13, U_ISOCAN.20
ISO_GND_485: C_H_ADM2.2, J_RS485_IN_H.3, J_RS485_OUT_H.3, U_RS485.11, U_RS485.13, U_RS485.15
ISO_GND_CAN: C_H_ISO2.2, J_CAN_IN_H.3, J_CAN_OUT_H.3, U_ISOCAN.11, U_ISOCAN.15, U_ISOCAN.16, U_ISOCAN.17
MCU_NRST: J_SWD_H.3, R_H_NRST.2, U_MCU.4
MCU_SWCLK: J_SWD_H.2, U_MCU.35
MCU_SWDIO: J_SWD_H.1, U_MCU.34
NACELLE_FB: R_FB_N1.2, R_FB_N2.1, U_BEC_NACELLE_12V.12
NACELLE_OUT: C_N_OUT.1, J_NACELLE_12V.3, J_NACELLE_12V.4, L_N.2, R_FB_N1.1, U_BEC_NACELLE_12V.9
PDB_ALERT_N: J_ALERT.2, R_ALERT.2, U_IS1.7, U_IS2.7, U_IS3.7, U_IS4.7, U_IS_MAIN.7
PDB_SCL: D_I2C.6, J_I2C.3, U_IS1.6, U_IS2.6, U_IS3.6, U_IS4.6, U_IS4.9, U_IS_MAIN.6, U_MCU.2
PDB_SDA: D_I2C.2, D_I2C.5, J_I2C.4, U_IS1.5, U_IS2.5, U_IS3.5, U_IS3.9, U_IS4.5, U_IS_MAIN.5, U_MCU.1
RCS6V_RAW: C_FFRCS.1, C_RCS_OUT.1, J_RCS_6V.3, J_RCS_6V.4, L_RCS.2, R_FBRCS_1.1, U_BEC_RCS_6V.13
RCS_FB: C_FFRCS.2, R_FBRCS_1.2, R_FBRCS_2.1, U_BEC_RCS_6V.12
RS485_A: J_RS485_IN_H.1, J_RS485_OUT_H.1, R_H_485TERM.1, U_RS485.17, U_RS485.20
RS485_B: J_RS485_IN_H.2, J_RS485_OUT_H.2, SJ_H_485.2, U_RS485.18, U_RS485.19
RS485_DE: U_MCU.14, U_RS485.3, U_RS485.5
RS485_FLT_N: U_MCU.15, U_RS485.8
RS485_RX: U_MCU.26, U_RS485.4
RS485_TX: U_MCU.25, U_RS485.2
RS_MAIN_SN: RS_MAIN.3, U_IS_MAIN.2
RS_MAIN_SP: RS_MAIN.2, U_IS_MAIN.1
SERVO_6V: C_BEC_SV_OUT.1, C_FFSV.1, J_SERVO_5V.3, J_SERVO_5V.4, J_WINCH_6V.3, J_WINCH_6V.4, L4.2, R_FBSV_1.1, U_BEC_SERVO_5V.13
TERM485_MID_H: R_H_485TERM.2, SJ_H_485.1
TPM_PIRQ: U_MCU.9, U_MCU.21, U_TPM.18
TPM_RESET_N: R_H_TPM_RST.2, U_MCU.13, U_MCU.22, U_TPM.17
TPM_SPI_CS: U_MCU.8, U_MCU.17, U_TPM.20
TPM_SPI_MISO: U_MCU.10, U_MCU.20, U_TPM.24
TPM_SPI_MOSI: U_MCU.11, U_MCU.19, U_TPM.21
TPM_SPI_SCK: U_MCU.12, U_MCU.18, U_TPM.19
U_BEC_5V_1_BIAS: C_BIAS1.1, U_BEC_5V_1.11
U_BEC_5V_1_BST: C_BOOT1.1, U_BEC_5V_1.2
U_BEC_5V_1_LX: C_BOOT1.2, L1.1, U_BEC_5V_1.6
U_BEC_5V_2_BIAS: C_BIAS2.1, U_BEC_5V_2.11
U_BEC_5V_2_BST: C_BOOT2.1, U_BEC_5V_2.2
U_BEC_5V_2_LX: C_BOOT2.2, L2.1, U_BEC_5V_2.6
U_BEC_NACELLE_12V_BOOT: C_N_BOOT.1, U_BEC_NACELLE_12V.6
U_BEC_NACELLE_12V_SW: C_N_BOOT.2, L_N.1, U_BEC_NACELLE_12V.1, U_BEC_NACELLE_12V.2, U_BEC_NACELLE_12V.3, U_BEC_NACELLE_12V.4, U_BEC_NACELLE_12V.5
U_BEC_NACELLE_12V_VCC: C_N_VCC.1, U_BEC_NACELLE_12V.8
U_BEC_RCS_6V_BIAS: C_BIAS_RCS.1, U_BEC_RCS_6V.11
U_BEC_RCS_6V_BST: C_BOOT_RCS.1, U_BEC_RCS_6V.2
U_BEC_RCS_6V_LX: C_BOOT_RCS.2, L_RCS.1, U_BEC_RCS_6V.6
U_BEC_SERVO_5V_BIAS: C_BIASSV.1, U_BEC_SERVO_5V.11
U_BEC_SERVO_5V_BST: C_BOOT_SV.1, U_BEC_SERVO_5V.2
U_BEC_SERVO_5V_LX: C_BOOT_SV.2, L4.1, U_BEC_SERVO_5V.6
U_REG_H_FB: R_H_FBB.1, R_H_FBT.2, U_REG_3V3_H.5
U_REG_H_SW: L_H1.1, U_REG_3V3_H.3
VBAT: C1.1, C2.1, C3.1, C_DM1.1, C_Y1.1, D1.1, F1.2, Q_BATT_DSG.3, Q_BATT_DSG.4, RS_MAIN.1
VBAT_IN_N: CM1.2, J_BATT.2
VBAT_IN_P: CM1.1, J_BATT.1
VDIS: C_BEC1_IN.1, C_BEC2_IN.1, C_BEC_SV_IN.1, C_N_IN.1, C_RCS_IN.1, F_ESC1.1, F_ESC2.1, F_ESC3.1, F_ESC4.1, Q_BATT_DSG.5, Q_BATT_DSG.6, Q_BATT_DSG.7, RS_MAIN.4, U_BEC_5V_1.1, U_BEC_5V_1.3, U_BEC_5V_1.9, U_BEC_5V_2.1, U_BEC_5V_2.3, U_BEC_5V_2.9, U_BEC_NACELLE_12V.18, U_BEC_NACELLE_12V.20, U_BEC_NACELLE_12V.21, U_BEC_NACELLE_12V.22, U_BEC_RCS_6V.1, U_BEC_RCS_6V.3, U_BEC_RCS_6V.9, U_BEC_SERVO_5V.1, U_BEC_SERVO_5V.3, U_BEC_SERVO_5V.9

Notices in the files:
avionics/kicad/Jayne/kicads/Jayne.kicad_pcb:
CC BY 4.0 creativecommons.org/licenses/by/4.0
Griffing Technology LLC | CC BY 4.0
avionics/kicad/Jayne/kicads/Jayne.kicad_sch:
Copyright 2026 Steve Griffing PE(CSE) CISSP-ISSEP CPP | Griffing Technology LLC
License: CC BY 4.0  |  creativecommons.org/licenses/by/4.0
avionics/kicad/Kaylee/kicads/Kaylee.kicad_pcb:
CC BY 4.0 -- July 2026
avionics/kicad/Pilot/kicads/Wash.kicad_pcb:
Hull: misubisu CC BY 4.0 | Nozzle: BamJr CC BY 4.0 | Firefly/Serenity fan-work, not officially licensed
CC BY 4.0 — May 2026
